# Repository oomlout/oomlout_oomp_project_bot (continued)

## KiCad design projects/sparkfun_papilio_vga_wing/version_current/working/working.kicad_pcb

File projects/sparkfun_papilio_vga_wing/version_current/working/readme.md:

# Papilio_VGA_Wing by sparkfun  
This is a harvested standardized copy of a project from github.  
The original project can be found at:  
https://github.com/sparkfun/Papilio_VGA_Wing  
Please consult that link for additional, details, files, and license information.  
Note: It was auto harvested and if the original repo had more than one board file or anything out of the ordinary the files here are likely not representative.

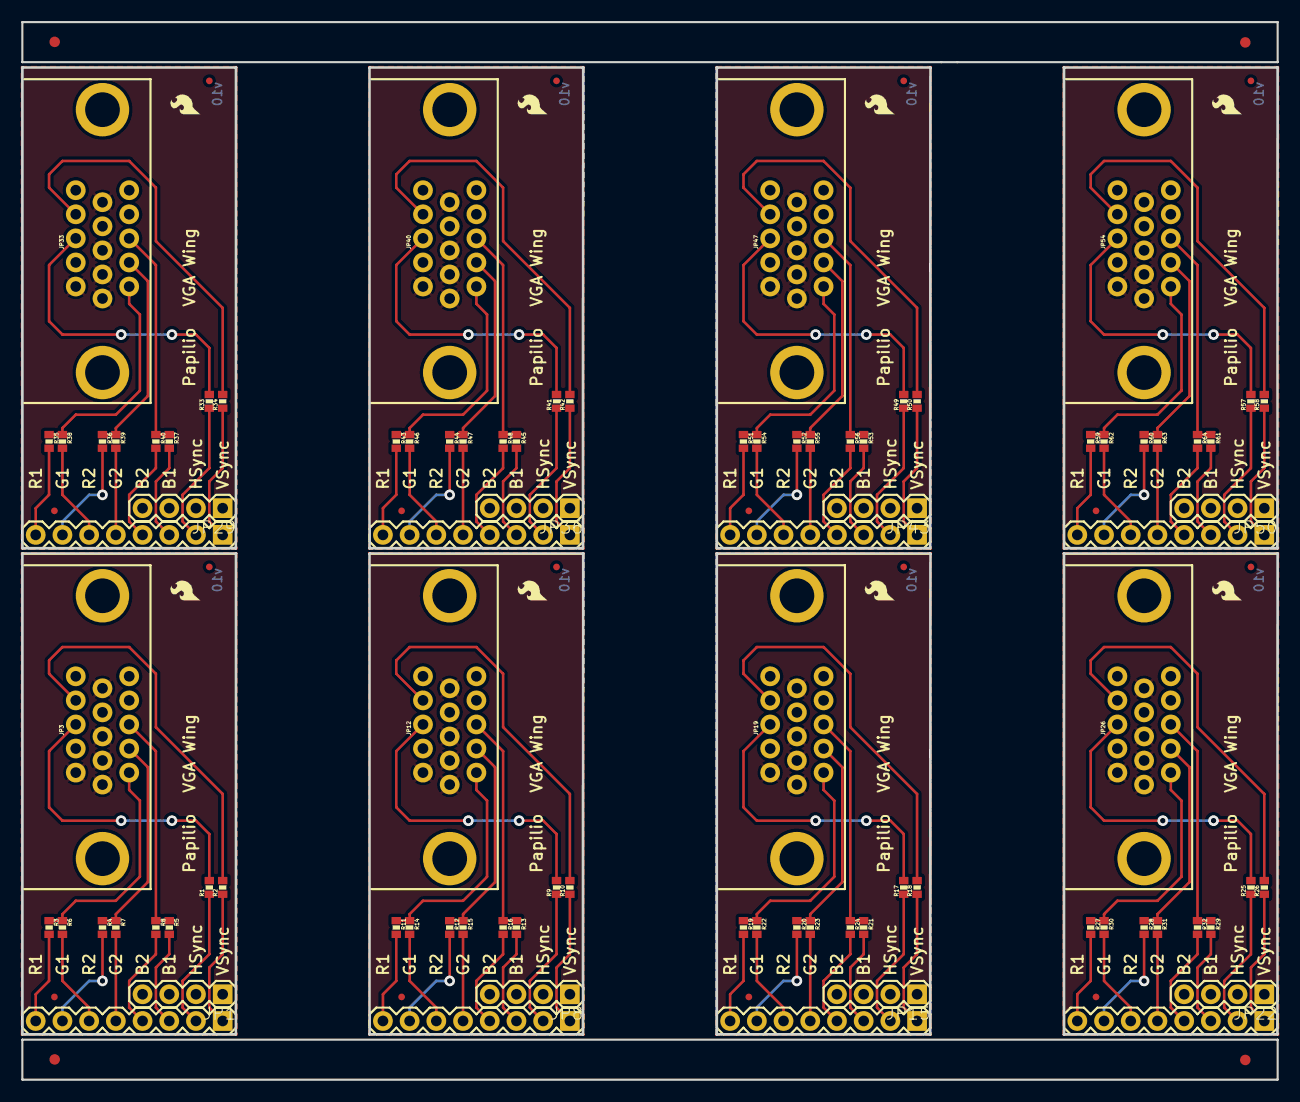
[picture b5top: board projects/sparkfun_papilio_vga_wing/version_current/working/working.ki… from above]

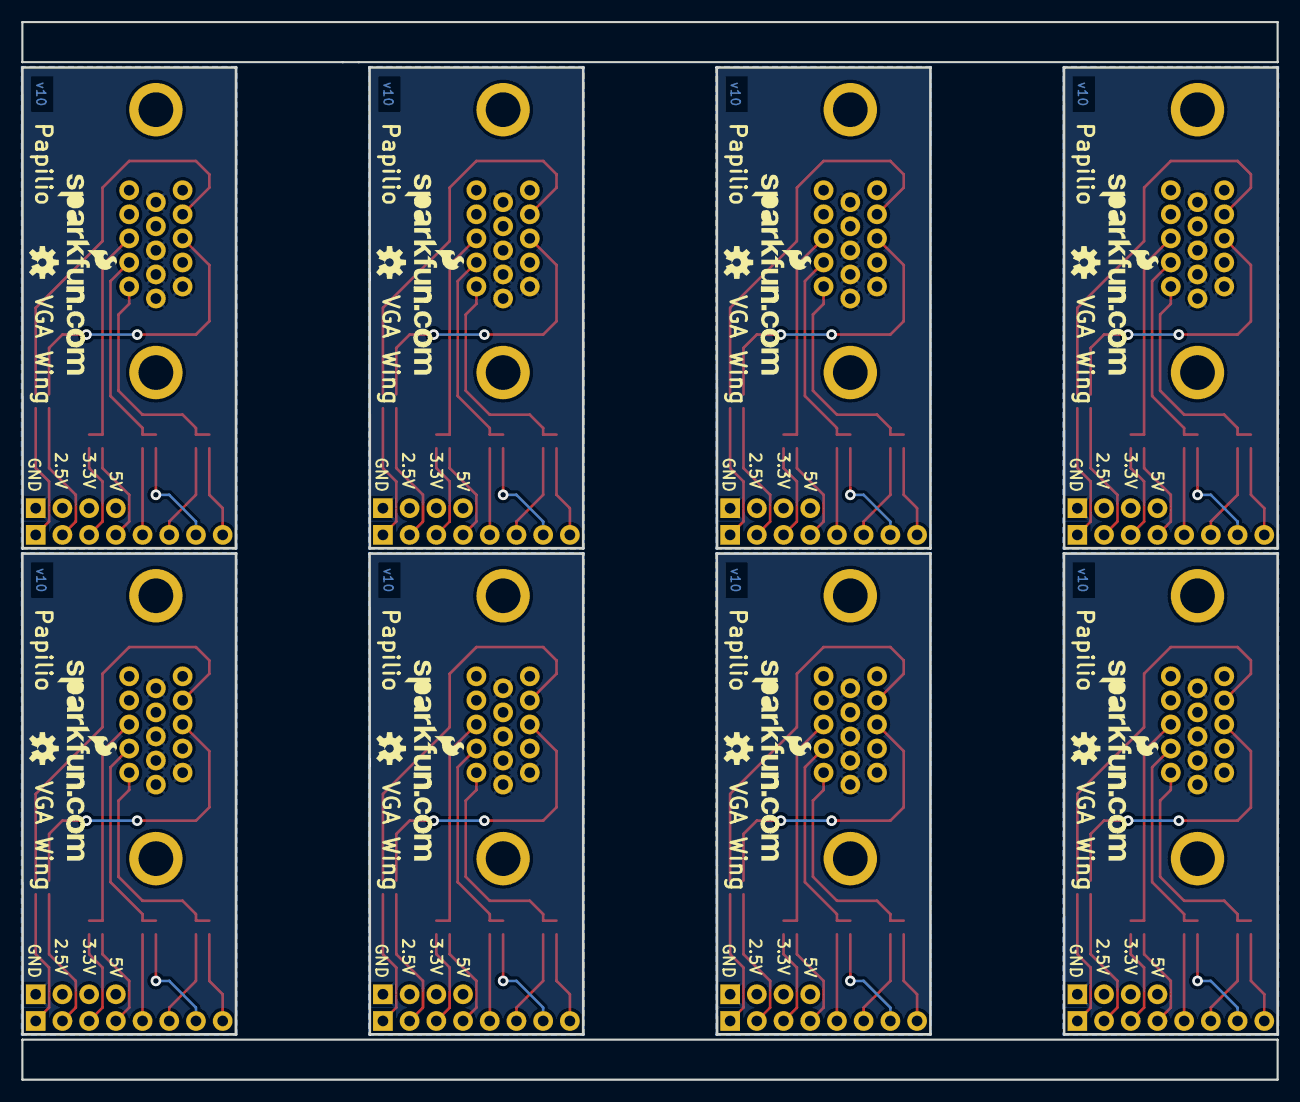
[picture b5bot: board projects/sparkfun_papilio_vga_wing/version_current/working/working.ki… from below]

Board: 2 copper layers, 119.4 x 100.6 mm, 132 parts (16 on the bottom side), 112 nets.

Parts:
E$1, E$2, E$3, E$4: FIDUCIAL-1X2
JP1, JP8, JP15, JP22, JP29, JP36, JP43, JP50: 1X04
JP2, JP9, JP16, JP23, JP30, JP37, JP44, JP51: 1X08
JP3, JP12, JP19, JP26, JP33, JP40, JP47, JP54: DB15
JP4, JP5, JP13, JP14, JP20, JP21, JP27, JP28, JP34, JP35, JP41, JP42, JP48, JP49, JP55, JP56: FIDUCIALUFIDUCIAL; MICRO-FIDUCIAL
JP6, JP11, JP18, JP25, JP32, JP39, JP46, JP53: LOGO-SFENEW; SFE-NEW-WEBLOGO
JP7, JP10, JP17, JP24, JP31, JP38, JP45, JP52: LOGO-SFESK; SFE-LOGO-FLAME
R1, R2, R9, R10, R17, R18, R25, R26, R33, R34, R41, R42, R49, R50, R57, R58: 82.5; 0402-RES
R3, R4, R5, R6, R7, R8, R11, R12, R13, R14, R15, R16, R19, R20, R21, R22, R23, R24, R27, R28, R29, R30, R31, R32, R35, R36, R37, R38, R39, R40, R43, R44, R45, R46, R47, R48, R51, R52, R53, R54, R55, R56, R59, R60, R61, R62, R63, R64: 270; 0402-RES
U$1, U$2, U$3, U$4, U$5, U$6, U$7, U$8: OSHW-LOGOS; OSHW-LOGO-S

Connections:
BLUE: JP3.3, R5.1, R8.1
BLUE1: JP2.3, R5.2
BLUE2: JP2.4, R8.2
BLUE3: JP9.3, R13.2
BLUE4: JP9.4, R16.2
BLUE5: JP12.3, R13.1, R16.1
BLUE6: JP16.3, R21.2
BLUE7: JP16.4, R24.2
BLUE8: JP19.3, R21.1, R24.1
BLUE9: JP23.3, R29.2
BLUE10: JP23.4, R32.2
BLUE11: JP26.3, R29.1, R32.1
BLUE12: JP30.3, R37.2
BLUE13: JP30.4, R40.2
BLUE14: JP33.3, R37.1, R40.1
BLUE15: JP37.3, R45.2
BLUE16: JP37.4, R48.2
BLUE17: JP40.3, R45.1, R48.1
BLUE18: JP44.3, R53.2
BLUE19: JP44.4, R56.2
BLUE20: JP47.3, R53.1, R56.1
BLUE21: JP51.3, R61.2
BLUE22: JP51.4, R64.2
BLUE23: JP54.3, R61.1, R64.1
GND: JP1.1, JP3.6, JP3.7, JP3.8, JP3.10, JP3.11
GND1: JP8.1, JP12.6, JP12.7, JP12.8, JP12.10, JP12.11
GND2: JP15.1, JP19.6, JP19.7, JP19.8, JP19.10, JP19.11
GND3: JP22.1, JP26.6, JP26.7, JP26.8, JP26.10, JP26.11
GND4: JP29.1, JP33.6, JP33.7, JP33.8, JP33.10, JP33.11
GND5: JP36.1, JP40.6, JP40.7, JP40.8, JP40.10, JP40.11
GND6: JP43.1, JP47.6, JP47.7, JP47.8, JP47.10, JP47.11
GND7: JP50.1, JP54.6, JP54.7, JP54.8, JP54.10, JP54.11
GREEN: JP3.2, R4.1, R7.1
GREEN1: JP2.7, R4.2
GREEN2: JP2.5, R7.2
GREEN3: JP9.7, R12.2
GREEN4: JP9.5, R15.2
GREEN5: JP12.2, R12.1, R15.1
GREEN6: JP16.7, R20.2
GREEN7: JP16.5, R23.2
GREEN8: JP19.2, R20.1, R23.1
GREEN9: JP23.7, R28.2
GREEN10: JP23.5, R31.2
GREEN11: JP26.2, R28.1, R31.1
GREEN12: JP30.7, R36.2
GREEN13: JP30.5, R39.2
GREEN14: JP33.2, R36.1, R39.1
GREEN15: JP37.7, R44.2
GREEN16: JP37.5, R47.2
GREEN17: JP40.2, R44.1, R47.1
GREEN18: JP44.7, R52.2
GREEN19: JP44.5, R55.2
GREEN20: JP47.2, R52.1, R55.1
GREEN21: JP51.7, R60.2
GREEN22: JP51.5, R63.2
GREEN23: JP54.2, R60.1, R63.1
HSYNC: JP2.2, R1.1
HSYNC1: JP9.2, R9.1
HSYNC2: JP16.2, R17.1
HSYNC3: JP23.2, R25.1
HSYNC4: JP30.2, R33.1
HSYNC5: JP37.2, R41.1
HSYNC6: JP44.2, R49.1
HSYNC7: JP51.2, R57.1
unnamed: JP12.13, R9.2
unnamed: JP3.13, R1.2
unnamed: JP3.14, R2.2
unnamed: JP12.14, R10.2
unnamed: JP19.13, R17.2
unnamed: JP19.14, R18.2
unnamed: JP26.13, R25.2
unnamed: JP26.14, R26.2
unnamed: JP33.13, R33.2
unnamed: JP33.14, R34.2
unnamed: JP40.13, R41.2
unnamed: JP40.14, R42.2
unnamed: JP47.13, R49.2
unnamed: JP47.14, R50.2
unnamed: JP54.13, R57.2
unnamed: JP54.14, R58.2
RED: JP3.1, R3.1, R6.1
RED1: JP2.8, R3.2
RED2: JP2.6, R6.2
RED3: JP9.8, R11.2
RED4: JP9.6, R14.2
RED5: JP12.1, R11.1, R14.1
RED6: JP16.8, R19.2
RED7: JP16.6, R22.2
RED8: JP19.1, R19.1, R22.1
RED9: JP23.8, R27.2
RED10: JP23.6, R30.2
RED11: JP26.1, R27.1, R30.1
RED12: JP30.8, R35.2
RED13: JP30.6, R38.2
RED14: JP33.1, R35.1, R38.1
RED15: JP37.8, R43.2
RED16: JP37.6, R46.2
RED17: JP40.1, R43.1, R46.1
RED18: JP44.8, R51.2
RED19: JP44.6, R54.2
RED20: JP47.1, R51.1, R54.1
RED21: JP51.8, R59.2
RED22: JP51.6, R62.2
RED23: JP54.1, R59.1, R62.1
VSYNC: JP2.1, R2.1
VSYNC1: JP9.1, R10.1
VSYNC2: JP16.1, R18.1
VSYNC3: JP23.1, R26.1
VSYNC4: JP30.1, R34.1
VSYNC5: JP37.1, R42.1
VSYNC6: JP44.1, R50.1
VSYNC7: JP51.1, R58.1

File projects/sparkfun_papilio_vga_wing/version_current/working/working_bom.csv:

Row,Description,Part,References,Value,Footprint,Quantity Per PCB,Status,Datasheet
1,,FRAME-LETTER,FRAME1,FRAME-LETTER,CREATIVE_COMMONS,1, ,
2,,DB15,JP3,DB15,DB15,1, ,
3,,LOGO-SFENEW,JP6,LOGO-SFENEW,SFE-NEW-WEBLOGO,1, ,
4,,LOGO-SFESK,JP7,LOGO-SFESK,SFE-LOGO-FLAME,1, ,
5,,M04PTH,JP1,M04PTH,1X04,1, ,
6,,M081X08,JP2,M081X08,1X08,1, ,
7,,RESISTOR0402-RES,R1 R2,82.5,0402-RES,2, ,
8,,RESISTOR0402-RES,R3 R4 R5 R6 R7 R8,270,0402-RES,6, ,
9,,OSHW-LOGOS,U$1,OSHW-LOGOS,OSHW-LOGO-S,1, ,





Project info:
Schematic:,working
Variant:,default
Revision:,
Date:,2023-08-06_12-56-12
KiCad Version:,7.0.6-7.0.6~ubuntu22.04.1
Statistics:
Component Groups:,9
Component Count:,15 (0 SMD/ 0 THT)
Fitted Components:,15 (0 SMD/ 0 THT)
Number of PCBs:,1
Total Components:,15

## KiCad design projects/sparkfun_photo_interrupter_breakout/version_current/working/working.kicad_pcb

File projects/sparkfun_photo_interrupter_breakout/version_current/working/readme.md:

# OOMP Project  
## Photo_Interrupter_Breakout  by sparkfun  
  
oomp key: oomp_projects_flat_sparkfun_photo_interrupter_breakout  
(snippet of original readme)  
  
Photo_Interrupter_Breakout  
==========================  
  
[  
*Photo Interrupter Breakout Board (BOB-09322)*](https://www.sparkfun.com/products/9322)  
  
Photo Interrupter Breakout Board - GP1A57HRJ00F available from SparkFun Electronics.   

Repository Contents  
-------------------  
* **/Firmware** - Any firmware that the part ships with,   
* **/Hardware** - All Eagle design files (.brd, .sch)  

License Information  
-------------------  
The hardware is released under [Creative Commons ShareAlike 4.0 International](https://creativecommons.org/licenses/by-sa/4.0/).  
The code is beerware; if you see me (or any other SparkFun employee) at the local, and you've found our code helpful, please buy us a round!  
  
Distributed as-is; no warranty is given.  
  
  full source readme at [readme_src.md](readme_src.md)  
  
source repo at: [https://github.com/sparkfun/Photo_Interrupter_Breakout](https://github.com/sparkfun/Photo_Interrupter_Breakout)  
## Board  

## Schematic  

[schematic pdf](working_schematic.pdf)  
## Images

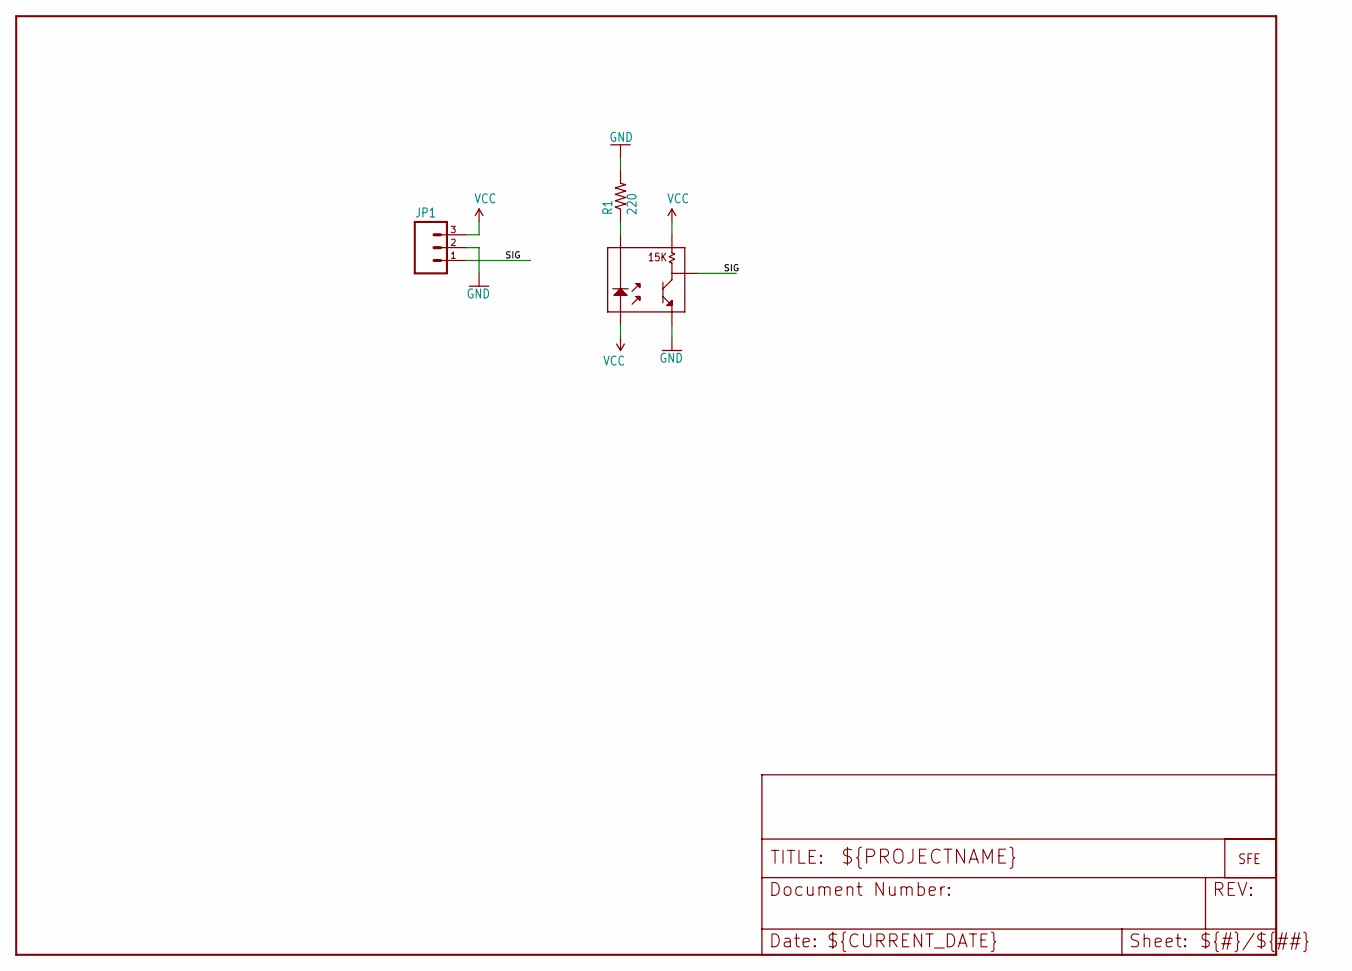
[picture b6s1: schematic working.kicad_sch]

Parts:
JP1: M03PTH; 1X03
R1: 220; AXIAL-0.3
U1: GP1A57HR
U2: LOGO-SFESK; SFE-LOGO-FLAME

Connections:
GND: JP1.2, R1.P$2 (2), U1.5
unnamed: R1.P$1 (1), U1.2
SIG: JP1.1, U1.4
VCC: JP1.3, U1.1, U1.3

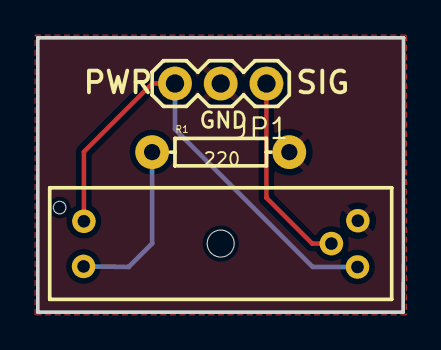
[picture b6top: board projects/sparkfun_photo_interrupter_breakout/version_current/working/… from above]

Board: 2 copper layers, 20.3 x 15.2 mm, 4 parts (1 on the bottom side), 4 nets.

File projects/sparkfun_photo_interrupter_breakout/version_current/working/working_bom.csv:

Row,Description,Part,References,Value,Footprint,Quantity Per PCB,Status,Datasheet
1,,M03PTH,JP1,M03PTH,1X03,1, ,
2,,RESISTORPTH1,R1,220,AXIAL-0.3,1, ,
3,,GP1A57HR,U1,GP1A57HR,GP1A57HR,1, ,
4,,LOGO-SFESK,U2,LOGO-SFESK,SFE-LOGO-FLAME,1, ,





Project info:
Schematic:,working
Variant:,default
Revision:,
Date:,2023-08-06_12-56-12
KiCad Version:,7.0.6-7.0.6~ubuntu22.04.1
Statistics:
Component Groups:,4
Component Count:,4 (0 SMD/ 0 THT)
Fitted Components:,4 (0 SMD/ 0 THT)
Number of PCBs:,1
Total Components:,4

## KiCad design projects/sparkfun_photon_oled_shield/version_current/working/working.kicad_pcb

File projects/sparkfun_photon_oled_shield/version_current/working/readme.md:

# Photon_OLED_Shield by sparkfun  
This is a harvested standardized copy of a project from github.  
The original project can be found at:  
https://github.com/sparkfun/Photon_OLED_Shield  
Please consult that link for additional, details, files, and license information.  
Note: It was auto harvested and if the original repo had more than one board file or anything out of the ordinary the files here are likely not representative.

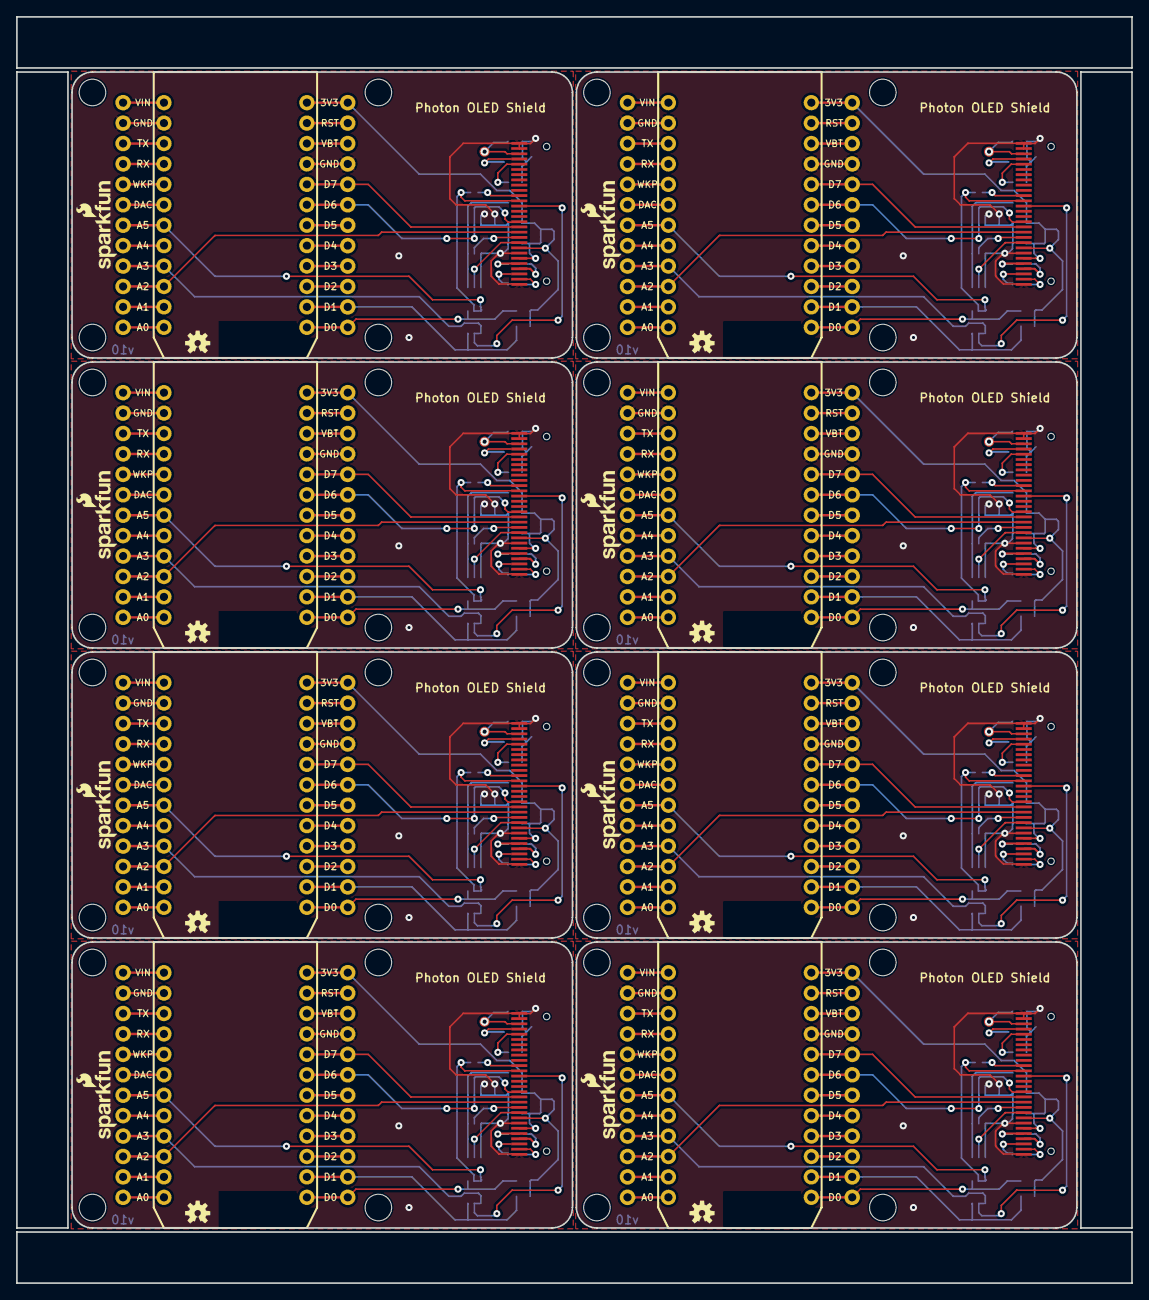
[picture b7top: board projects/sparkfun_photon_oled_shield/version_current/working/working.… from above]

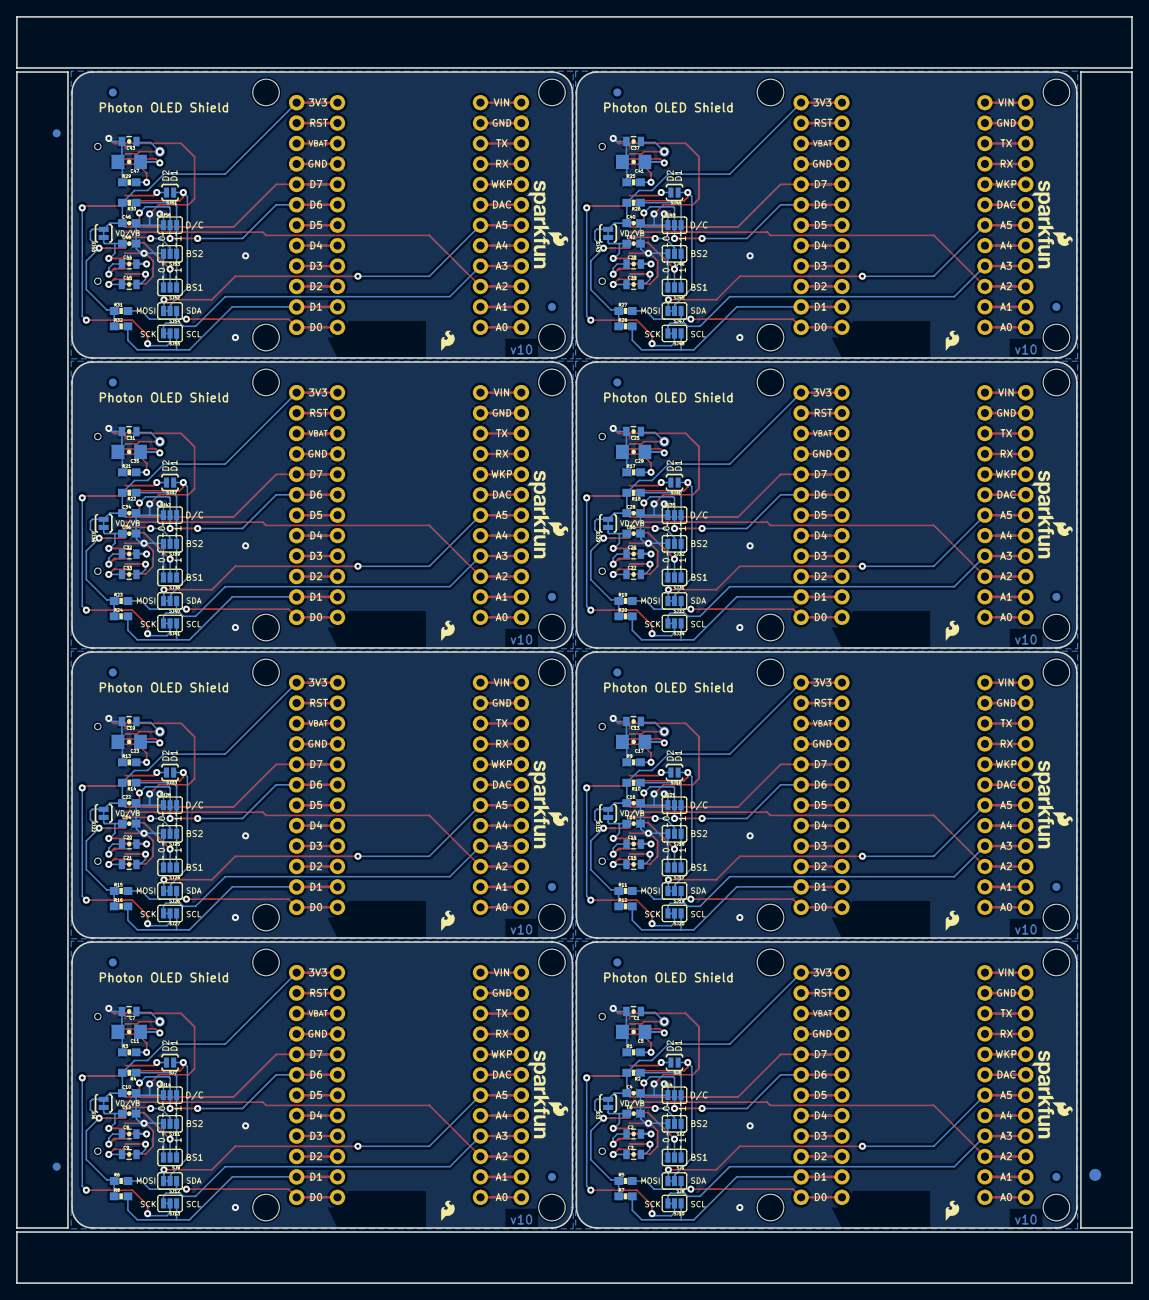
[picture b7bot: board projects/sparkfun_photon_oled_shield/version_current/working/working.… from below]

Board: 2 copper layers, 138.7 x 157.5 mm, 219 parts (179 on the bottom side), 240 nets.

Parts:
C1, C7, C13, C19, C25, C31, C37, C43: 2.2uF; 0805-CAP
C2, C3, C8, C9, C14, C15, C20, C21, C26, C27, C32, C33, C38, C39, C44, C45: 1uF; 0805-CAP
C4, C6, C10, C12, C16, C18, C22, C24, C28, C30, C34, C36, C40, C42, C46, C48: 1uF; 0603-CAP
C5, C11, C17, C23, C29, C35, C41, C47: 4.7uF; 1206-CAP
E$1: FIDUCIAL-1.5X3
E$4, E$5: FIDUCIAL-1X2
FID1, FID2, FID3, FID4, FID5, FID6, FID7, FID8, FID9, FID10, FID11, FID12, FID13, FID14, FID15, FID16: FIDUCIAL1X2; FIDUCIAL-1X2
JP1, JP2, JP3, JP4, JP5, JP6, JP7, JP8: SPARK_PHOTONTEMPLATE_WIDE; SPARK_PHOTON_TEMPLATE_WIDE
LOGO1, LOGO2, LOGO5, LOGO6, LOGO8, LOGO9, LOGO11, LOGO12, LOGO14, LOGO15, LOGO17, LOGO18, LOGO20, LOGO21, LOGO23, LOGO24: SFE_LOGO_NAME_FLAME.1_INCH; SFE_LOGO_NAME_FLAME_.1
LOGO3, LOGO4, LOGO7, LOGO10, LOGO13, LOGO16, LOGO19, LOGO22: OSHW-LOGOS; OSHW-LOGO-S
OLED1, OLED2, OLED3, OLED4, OLED5, OLED6, OLED7, OLED8: OLED0.66; OLED-0.66-64X48
R1, R3, R9, R13, R17, R21, R25, R29: 390k; 0603-RES
R2, R4, R10, R14, R18, R22, R26, R30: 10k; 0603-RES
R5, R6, R7, R8, R11, R12, R15, R16, R19, R20, R23, R24, R27, R28, R31, R32: 10K; 0603-RES
SJ1, SJ9, SJ17, SJ24, SJ31, SJ38, SJ45, SJ52: BS1; PAD-JUMPER-3-2OF3_NC_BY_PASTE_YES_SILK_FULL_BOX
SJ2, SJ11, SJ18, SJ25, SJ32, SJ39, SJ46, SJ53: BS2; PAD-JUMPER-3-2OF3_NC_BY_PASTE_YES_SILK_FULL_BOX
SJ3, SJ6, SJ15, SJ22, SJ29, SJ36, SJ43, SJ50: PAD-JUMPER-2-NC_BY_TRACE_YES_SILK
SJ4, SJ14, SJ21, SJ28, SJ35, SJ42, SJ49, SJ56: PAD-JUMPER-3-NO_YES_SILK
SJ5, SJ7, SJ16, SJ23, SJ30, SJ37, SJ44, SJ51: PAD-JUMPER-2-NO_YES_SILK
SJ8, SJ10, SJ12, SJ13, SJ19, SJ20, SJ26, SJ27, SJ33, SJ34, SJ40, SJ41, SJ47, SJ48, SJ54, SJ55: PAD-JUMPER-3-2OF3_NC_BY_TRACE_YES_SILK_FULL_BOX
TP1, TP2, TP3, TP4, TP5, TP6, TP7, TP8, TP9, TP10, TP11, TP12, TP13, TP14, TP15, TP16: TEST-POINT3X5; PAD.03X.05
U$1, U$2, U$3, U$4, U$5, U$6, U$7, U$8: SFE_LOGO_FLAME_.1

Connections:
BS1: OLED1.9, SJ1.2
BS2: OLED1.10, SJ2.2
BS3: OLED2.9, SJ9.2
BS4: OLED2.10, SJ11.2
BS5: OLED3.9, SJ17.2
BS6: OLED3.10, SJ18.2
BS7: OLED4.9, SJ24.2
BS8: OLED4.10, SJ25.2
BS9: OLED5.9, SJ31.2
BS10: OLED5.10, SJ32.2
BS11: OLED6.9, SJ38.2
BS12: OLED6.10, SJ39.2
BS13: OLED7.9, SJ45.2
BS14: OLED7.10, SJ46.2
BS15: OLED8.9, SJ52.2
BS16: OLED8.10, SJ53.2
C1N: C2.2, OLED1.5
C1N1: C8.2, OLED2.5
C1N2: C14.2, OLED3.5
C1N3: C20.2, OLED4.5
C1N4: C26.2, OLED5.5
C1N5: C32.2, OLED6.5
C1N6: C38.2, OLED7.5
C1N7: C44.2, OLED8.5
C1P: C2.1, OLED1.4
C1P1: C8.1, OLED2.4
C1P2: C14.1, OLED3.4
C1P3: C20.1, OLED4.4
C1P4: C26.1, OLED5.4
C1P5: C32.1, OLED6.4
C1P6: C38.1, OLED7.4
C1P7: C44.1, OLED8.4
C2N: C3.2, OLED1.3
C2N1: C9.2, OLED2.3
C2N2: C15.2, OLED3.3
C2N3: C21.2, OLED4.3
C2N4: C27.2, OLED5.3
C2N5: C33.2, OLED6.3
C2N6: C39.2, OLED7.3
C2N7: C45.2, OLED8.3
C2P: C3.1, OLED1.2
C2P1: C9.1, OLED2.2
C2P2: C15.1, OLED3.2
C2P3: C21.1, OLED4.2
C2P4: C27.1, OLED5.2
C2P5: C33.1, OLED6.2
C2P6: C39.1, OLED7.2
C2P7: C45.1, OLED8.2
D0/SCK: OLED1.16, SJ10.2
D0/SCK1: OLED2.16, SJ13.2
D0/SCK2: OLED3.16, SJ20.2
D0/SCK3: OLED4.16, SJ27.2
D0/SCK4: OLED5.16, SJ34.2
D0/SCK5: OLED6.16, SJ41.2
D0/SCK6: OLED7.16, SJ48.2
D0/SCK7: OLED8.16, SJ55.2
D0/SDA: JP3.13, JP3.D0, R5.2, SJ8.1
D0/SDA1: JP1.13, JP1.D0, R6.2, SJ12.1
D0/SDA2: JP2.13, JP2.D0, R11.2, SJ19.1
D0/SDA3: JP4.13, JP4.D0, R15.2, SJ26.1
D0/SDA4: JP5.13, JP5.D0, R19.2, SJ33.1
D0/SDA5: JP6.13, JP6.D0, R23.2, SJ40.1
D0/SDA6: JP7.13, JP7.D0, R27.2, SJ47.1
D0/SDA7: JP8.13, JP8.D0, R31.2, SJ54.1
D1: JP1.20, JP1.D7, OLED2.12
D1/MOSI: OLED1.17, SJ5.1, SJ8.2
D1/MOSI1: OLED2.17, SJ7.1, SJ12.2
D1/MOSI2: OLED3.17, SJ16.1, SJ19.2
D1/MOSI3: OLED4.17, SJ23.1, SJ26.2
D1/MOSI4: OLED5.17, SJ30.1, SJ33.2
D1/MOSI5: OLED6.17, SJ37.1, SJ40.2
D1/MOSI6: OLED7.17, SJ44.1, SJ47.2
D1/MOSI7: OLED8.17, SJ51.1, SJ54.2
D1/SCL: JP3.14, JP3.D1, R7.2, SJ10.1
D1/SCL1: JP1.14, JP1.D1, R8.2, SJ13.1
D1/SCL2: JP2.14, JP2.D1, R12.2, SJ20.1
D1/SCL3: JP4.14, JP4.D1, R16.2, SJ27.1
D1/SCL4: JP5.14, JP5.D1, R20.2, SJ34.1
D1/SCL5: JP6.14, JP6.D1, R24.2, SJ41.1
D1/SCL6: JP7.14, JP7.D1, R28.2, SJ48.1
D1/SCL7: JP8.14, JP8.D1, R32.2, SJ55.1
D2: JP3.15, JP3.D2
D2/MISO: OLED1.18, SJ5.2
D2/MISO1: OLED2.18, SJ7.2
D2/MISO2: OLED3.18, SJ16.2
D2/MISO3: OLED4.18, SJ23.2
D2/MISO4: OLED5.18, SJ30.2
D2/MISO5: OLED6.18, SJ37.2
D2/MISO6: OLED7.18, SJ44.2
D2/MISO7: OLED8.18, SJ51.2
D3: JP3.16, JP3.D3
D4: JP3.17, JP3.D4
D5: JP3.18, JP3.D5
D6: JP3.19, JP3.D6, OLED1.13, SJ4.2
D7: JP3.20, JP3.D7, OLED1.12
D8: JP1.19, JP1.D6, OLED2.13, SJ14.2
D9: JP1.18, JP1.D5
D10: JP1.17, JP1.D4
D11: JP1.15, JP1.D2
D12: JP1.16, JP1.D3
D13: JP2.20, JP2.D7, OLED3.12
D14: JP2.19, JP2.D6, OLED3.13, SJ21.2
D15: JP2.18, JP2.D5
D16: JP2.17, JP2.D4
D17: JP2.15, JP2.D2
D18: JP2.16, JP2.D3
D19: JP4.20, JP4.D7, OLED4.12
D20: JP4.19, JP4.D6, OLED4.13, SJ28.2
D21: JP4.18, JP4.D5
D22: JP4.17, JP4.D4
D23: JP4.15, JP4.D2
D24: JP4.16, JP4.D3
D25: JP5.20, JP5.D7, OLED5.12
D26: JP5.19, JP5.D6, OLED5.13, SJ35.2
D27: JP5.18, JP5.D5
D28: JP5.17, JP5.D4
D29: JP5.15, JP5.D2
D30: JP5.16, JP5.D3
D31: JP6.20, JP6.D7, OLED6.12
D32: JP6.19, JP6.D6, OLED6.13, SJ42.2
D33: JP6.18, JP6.D5
D34: JP6.17, JP6.D4
D35: JP6.15, JP6.D2
D36: JP6.16, JP6.D3
D37: JP7.20, JP7.D7, OLED7.12
D38: JP7.19, JP7.D6, OLED7.13, SJ49.2
D39: JP7.18, JP7.D5
D40: JP7.17, JP7.D4
D41: JP7.15, JP7.D2
D42: JP7.16, JP7.D3
D43: JP8.20, JP8.D7, OLED8.12
D44: JP8.19, JP8.D6, OLED8.13, SJ56.2
D45: JP8.18, JP8.D5
D46: JP8.17, JP8.D4
D47: JP8.15, JP8.D2
D48: JP8.16, JP8.D3
GND: C1.2, C4.2, C5.2, C6.2, JP3.2, JP3.21, JP3.GND@0, JP3.GND@2, OLED1.1, OLED1.7, OLED1.27, OLED1.28, R1.1, SJ1.3, SJ2.3, SJ4.1
GND1: C7.2, C10.2, C11.2, C12.2, JP1.2, JP1.21, JP1.GND@0, JP1.GND@2, OLED2.1, OLED2.7, OLED2.27, OLED2.28, R3.1, SJ9.3, SJ11.3, SJ14.1
GND2: C13.2, C16.2, C17.2, C18.2, JP2.2, JP2.21, JP2.GND@0, JP2.GND@2, OLED3.1, OLED3.7, OLED3.27, OLED3.28, R9.1, SJ17.3, SJ18.3, SJ21.1
GND3: C19.2, C22.2, C23.2, C24.2, JP4.2, JP4.21, JP4.GND@0, JP4.GND@2, OLED4.1, OLED4.7, OLED4.27, OLED4.28, R13.1, SJ24.3, SJ25.3, SJ28.1
GND4: C25.2, C28.2, C29.2, C30.2, JP5.2, JP5.21, JP5.GND@0, JP5.GND@2, OLED5.1, OLED5.7, OLED5.27, OLED5.28, R17.1, SJ31.3, SJ32.3, SJ35.1
GND5: C31.2, C34.2, C35.2, C36.2, JP6.2, JP6.21, JP6.GND@0, JP6.GND@2, OLED6.1, OLED6.7, OLED6.27, OLED6.28, R21.1, SJ38.3, SJ39.3, SJ42.1
GND6: C37.2, C40.2, C41.2, C42.2, JP7.2, JP7.21, JP7.GND@0, JP7.GND@2, OLED7.1, OLED7.7, OLED7.27, OLED7.28, R25.1, SJ45.3, SJ46.3, SJ49.1
GND7: C43.2, C46.2, C47.2, C48.2, JP8.2, JP8.21, JP8.GND@0, JP8.GND@2, OLED8.1, OLED8.7, OLED8.27, OLED8.28, R29.1, SJ52.3, SJ53.3, SJ56.1
IREF: OLED1.24, R1.2
IREF1: OLED2.24, R3.2
IREF2: OLED3.24, R9.2
IREF3: OLED4.24, R13.2
IREF4: OLED5.24, R17.2
IREF5: OLED6.24, R21.2
IREF6: OLED7.24, R25.2
IREF7: OLED8.24, R29.2
MISO: JP3.8, JP3.A4
MISO1: JP1.8, JP1.A4
MISO2: JP2.8, JP2.A4
MISO3: JP4.8, JP4.A4
MISO4: JP5.8, JP5.A4
MISO5: JP6.8, JP6.A4
MISO6: JP7.8, JP7.A4
MISO7: JP8.8, JP8.A4
MOSI: JP3.7, JP3.A5, SJ8.3
MOSI1: JP1.7, JP1.A5, SJ12.3
MOSI2: JP2.7, JP2.A5, SJ19.3
MOSI3: JP4.7, JP4.A5, SJ26.3
MOSI4: JP5.7, JP5.A5, SJ33.3
MOSI5: JP6.7, JP6.A5, SJ40.3
MOSI6: JP7.7, JP7.A5, SJ47.3
MOSI7: JP8.7, JP8.A5, SJ54.3
RESET: JP3.23, JP3.RST
RESET1: JP1.23, JP1.RST
RESET2: JP2.23, JP2.RST
RESET3: JP4.23, JP4.RST
RESET4: JP5.23, JP5.RST
RESET5: JP6.23, JP6.RST
RESET6: JP7.23, JP7.RST
RESET7: JP8.23, JP8.RST
SCK: JP3.9, JP3.A3, SJ10.3
SCK1: JP1.9, JP1.A3, SJ13.3
SCK2: JP2.9, JP2.A3, SJ20.3
SCK3: JP4.9, JP4.A3, SJ27.3
SCK4: JP5.9, JP5.A3, SJ34.3
SCK5: JP6.9, JP6.A3, SJ41.3
SCK6: JP7.9, JP7.A3, SJ48.3
SCK7: JP8.9, JP8.A3, SJ55.3
SS: JP3.10, JP3.A2, OLED1.11
SS1: JP1.10, JP1.A2, OLED2.11
SS2: JP2.10, JP2.A2, OLED3.11
SS3: JP4.10, JP4.A2, OLED4.11
SS4: JP5.10, JP5.A2, OLED5.11
SS5: JP6.10, JP6.A2, OLED6.11
SS6: JP7.10, JP7.A2, OLED7.11
SS7: JP8.10, JP8.A2, OLED8.11
VBAT: C6.1, OLED1.6, SJ3.1
VBAT1: C12.1, OLED2.6, SJ6.1
VBAT2: C18.1, OLED3.6, SJ15.1
VBAT3: C24.1, OLED4.6, SJ22.1
VBAT4: C30.1, OLED5.6, SJ29.1
VBAT5: C36.1, OLED6.6, SJ36.1
VBAT6: C42.1, OLED7.6, SJ43.1
VBAT7: C48.1, OLED8.6, SJ50.1
VBAT_PHOTON: JP3.22, JP3.VBAT
VBAT_PHOTON1: JP1.22, JP1.VBAT
VBAT_PHOTON2: JP2.22, JP2.VBAT
VBAT_PHOTON3: JP4.22, JP4.VBAT
VBAT_PHOTON4: JP5.22, JP5.VBAT
VBAT_PHOTON5: JP6.22, JP6.VBAT
VBAT_PHOTON6: JP7.22, JP7.VBAT
VBAT_PHOTON7: JP8.22, JP8.VBAT
VCC: C1.1, OLED1.26, TP1.P$1, TP2.P$1
VCC1: C7.1, OLED2.26, TP3.P$1, TP4.P$1
VCC2: C13.1, OLED3.26, TP5.P$1, TP6.P$1
VCC3: C19.1, OLED4.26, TP7.P$1, TP8.P$1
VCC4: C25.1, OLED5.26, TP9.P$1, TP10.P$1
VCC5: C31.1, OLED6.26, TP11.P$1, TP12.P$1
VCC6: C37.1, OLED7.26, TP13.P$1, TP14.P$1
VCC7: C43.1, OLED8.26, TP15.P$1, TP16.P$1
VCOMH: C5.1, OLED1.25
VCOMH1: C11.1, OLED2.25
VCOMH2: C17.1, OLED3.25
VCOMH3: C23.1, OLED4.25
VCOMH4: C29.1, OLED5.25
VCOMH5: C35.1, OLED6.25
VCOMH6: C41.1, OLED7.25
VCOMH7: C47.1, OLED8.25
VDD: C4.1, JP3.3V3, JP3.24, OLED1.8, R2.2, R5.1, R7.1, SJ3.2
VDD1: C10.1, JP1.3V3, JP1.24, OLED2.8, R4.2, R6.1, R8.1, SJ6.2
VDD2: C16.1, JP2.3V3, JP2.24, OLED3.8, R10.2, R11.1, R12.1, SJ15.2
VDD3: C22.1, JP4.3V3, JP4.24, OLED4.8, R14.2, R15.1, R16.1, SJ22.2
VDD4: C28.1, JP5.3V3, JP5.24, OLED5.8, R18.2, R19.1, R20.1, SJ29.2
VDD5: C34.1, JP6.3V3, JP6.24, OLED6.8, R22.2, R23.1, R24.1, SJ36.2
VDD6: C40.1, JP7.3V3, JP7.24, OLED7.8, R26.2, R27.1, R28.1, SJ43.2
VDD7: C46.1, JP8.3V3, JP8.24, OLED8.8, R30.2, R31.1, R32.1, SJ50.2
VDD_PU: R2.1, SJ1.1, SJ2.1, SJ4.3
VDD_PU1: R4.1, SJ9.1, SJ11.1, SJ14.3
VDD_PU2: R10.1, SJ17.1, SJ18.1, SJ21.3
VDD_PU3: R14.1, SJ24.1, SJ25.1, SJ28.3
VDD_PU4: R18.1, SJ31.1, SJ32.1, SJ35.3
VDD_PU5: R22.1, SJ38.1, SJ39.1, SJ42.3
VDD_PU6: R26.1, SJ45.1, SJ46.1, SJ49.3
VDD_PU7: R30.1, SJ52.1, SJ53.1, SJ56.3

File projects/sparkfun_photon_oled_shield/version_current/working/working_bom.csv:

Row,Description,Part,References,Value,Footprint,Quantity Per PCB,Status,Datasheet,PROD_ID
1,,1UF-25V-10%(0805){dblquote},C2 C3,1uF,0805-CAP,2, ,,
2,,CAP0603-CAP,C4 C6,1uF,0603-CAP,2, ,,CAP-00868
3,,2.2UF-25V-+80/-20(0805),C1,2.2uF,0805-CAP,1, ,,
4,,"4.7UF-16V-20%,+80%-(1206)",C5,4.7uF,1206-CAP,1, ,,CAP-10300
5,,FRAME-LETTER,FRAME1,FRAME-LETTER,CREATIVE_COMMONS,1, ,,
6,,SPARK_PHOTONTEMPLATE_WIDE,JP3,SPARK_PHOTONTEMPLATE_WIDE,SPARK_PHOTON_TEMPLATE_WIDE,1, ,,
7,,OSHW-LOGOS,LOGO3,OSHW-LOGOS,OSHW-LOGO-S,1, ,,
8,,SFE_LOGO_NAME_FLAME.1_INCH,LOGO1 LOGO2,SFE_LOGO_NAME_FLAME.1_INCH,SFE_LOGO_NAME_FLAME_.1,2, ,,
9,,OLED0.66,OLED1,OLED0.66,OLED-0.66-64X48,1, ,,LCD-12019
10,,RESISTOR0603-RES,R2,10k,0603-RES,1, ,,RES-00824
11,,10KOHM1/10W1%(0603)0603,R5 R7,10K,0603-RES,2, ,,
12,,RESISTOR0603-RES,R1,390k,0603-RES,1, ,,RES-12024
13,,JUMPER-PAD-2-NC_BY_TRACE,SJ3,JUMPER-PAD-2-NC_BY_TRACE,PAD-JUMPER-2-NC_BY_TRACE_YES_SILK,1, ,,
14,,JUMPER-PAD-2-NOYES_SILK,SJ5,JUMPER-PAD-2-NOYES_SILK,PAD-JUMPER-2-NO_YES_SILK,1, ,,
15,,JUMPER-PAD-3-2OF3_NC_BY_PASTE,SJ1 SJ2,JUMPER-PAD-3-2OF3_NC_BY_PASTE,PAD-JUMPER-3-2OF3_NC_BY_PASTE_YES_SILK_FULL_BOX,2, ,,
16,,JUMPER-PAD-3-2OF3_NC_BY_TRACE_SMALL,SJ8 SJ10,JUMPER-PAD-3-2OF3_NC_BY_TRACE_SMALL,PAD-JUMPER-3-2OF3_NC_BY_TRACE_YES_SILK_FULL_BOX,2, ,,
17,,JUMPER-PAD-3-NOYES_SILK,SJ4,JUMPER-PAD-3-NOYES_SILK,PAD-JUMPER-3-NO_YES_SILK,1, ,,





Project info:
Schematic:,working
Variant:,default
Revision:,
Date:,2023-08-06_12-56-12
KiCad Version:,7.0.6-7.0.6~ubuntu22.04.1
Statistics:
Component Groups:,17
Component Count:,23 (0 SMD/ 0 THT)
Fitted Components:,23 (0 SMD/ 0 THT)
Number of PCBs:,1
Total Components:,23

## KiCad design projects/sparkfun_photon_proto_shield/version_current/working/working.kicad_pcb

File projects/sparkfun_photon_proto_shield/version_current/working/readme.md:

# Photon_Proto_Shield by sparkfun  
This is a harvested standardized copy of a project from github.  
The original project can be found at:  
https://github.com/sparkfun/Photon_Proto_Shield  
Please consult that link for additional, details, files, and license information.  
Note: It was auto harvested and if the original repo had more than one board file or anything out of the ordinary the files here are likely not representative.

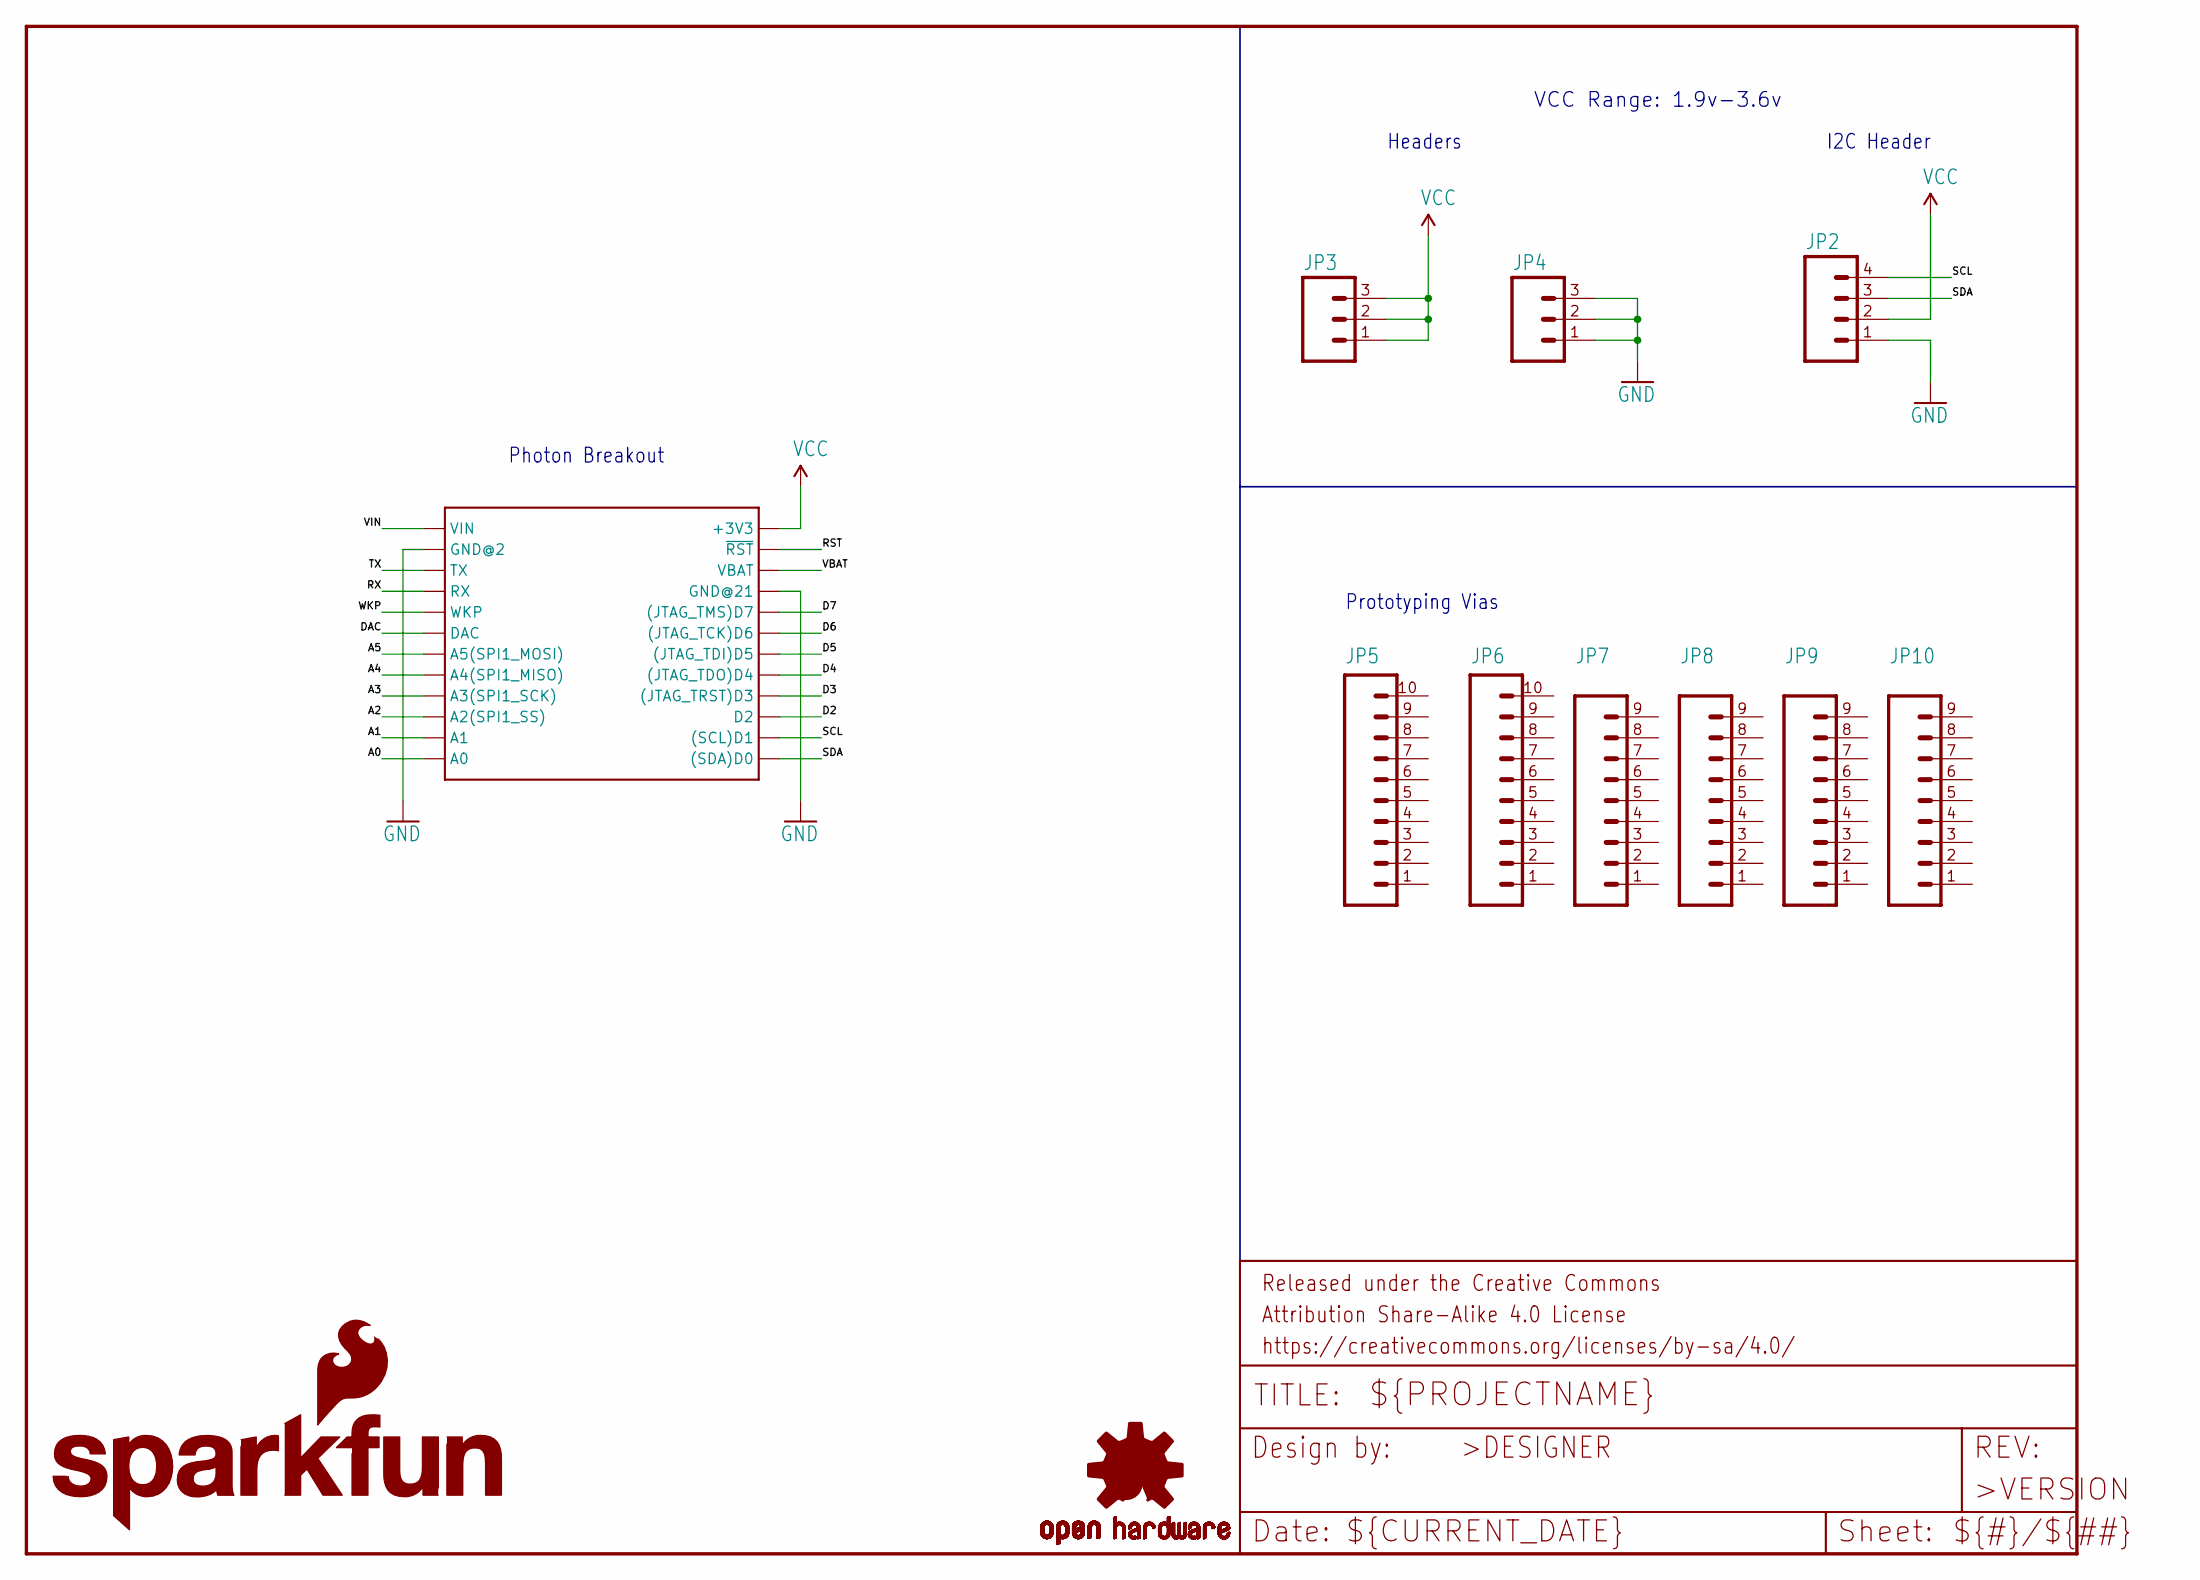
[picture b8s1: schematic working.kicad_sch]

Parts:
FRAME1: FRAME-LETTER; CREATIVE_COMMONS
JP1: SPARK_PHOTONTEMPLATE_WIDE; SPARK_PHOTON_TEMPLATE_WIDE
JP2: M04PTH; 1X04
JP3, JP4: M03PTH; 1X03
JP5, JP6: M10NO_SILK_PTH_FEMALE; 1X10_NO_SILK
JP7, JP8, JP9, JP10: M09NO_SILK; 1X09_NO_SILK
LOGO1: SFE_LOGO_NAME_FLAME.1_INCH; SFE_LOGO_NAME_FLAME_.1
LOGO2: OSHW-LOGOS; OSHW-LOGO-S

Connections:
A0: JP1.12 (A0), JP1.A0
A1: JP1.11 (A1), JP1.A1
A2: JP1.10 (A2(SPI1_SS)), JP1.A2 (A2(SPI1_SS))
A3: JP1.9 (A3(SPI1_SCK)), JP1.A3 (A3(SPI1_SCK))
A4: JP1.8 (A4(SPI1_MISO)), JP1.A4 (A4(SPI1_MISO))
A5: JP1.7 (A5(SPI1_MOSI)), JP1.A5 (A5(SPI1_MOSI))
D2: JP1.15 (D2), JP1.D2
D3: JP1.16 ((JTAG_TRST)D3), JP1.D3 ((JTAG_TRST)D3)
D4: JP1.17 ((JTAG_TDO)D4), JP1.D4 ((JTAG_TDO)D4)
D5: JP1.18 ((JTAG_TDI)D5), JP1.D5 ((JTAG_TDI)D5)
D6: JP1.19 ((JTAG_TCK)D6), JP1.D6 ((JTAG_TCK)D6)
D7: JP1.20 ((JTAG_TMS)D7), JP1.D7 ((JTAG_TMS)D7)
DAC: JP1.6 (DAC), JP1.DAC
GND: JP1.2 (GND@2), JP1.21 (GND@21), JP1.GND@0 (GND@2), JP1.GND@2 (GND@21), JP2.1, JP4.1, JP4.2, JP4.3
RST: JP1.23 (~RST), JP1.RST (~RST)
RX: JP1.4 (RX), JP1.RX
SCL: JP1.14 ((SCL)D1), JP1.D1 ((SCL)D1), JP2.4
SDA: JP1.13 ((SDA)D0), JP1.D0 ((SDA)D0), JP2.3
TX: JP1.3 (TX), JP1.TX
VBAT: JP1.22 (VBAT), JP1.VBAT
VCC: JP1.3V3 (+3V3), JP1.24 (+3V3), JP2.2, JP3.1, JP3.2, JP3.3
VIN: JP1.1 (VIN), JP1.VIN
WKP: JP1.5 (WKP), JP1.WKP

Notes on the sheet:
VCC Range: 1.9v-3.6v
Headers
Prototyping Vias
I2C Header
Photon Breakout
